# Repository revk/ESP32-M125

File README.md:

# ESP32-M125

This is hardware and software designed to be fitted within a Marsden M-125 set of medical scales.

Examples of modifications with much older prototype boards https://youtu.be/l1VAymhwtVMand  https://youtu.be/jy-5EB_Qu8Y

Takes data when SEND pressed and reports via MQTT and https. But can also work with an NFC board https://github.com/revk/ESP32-PN532 so tapping a card or tag will report ID and weight, pressing SEND for you.

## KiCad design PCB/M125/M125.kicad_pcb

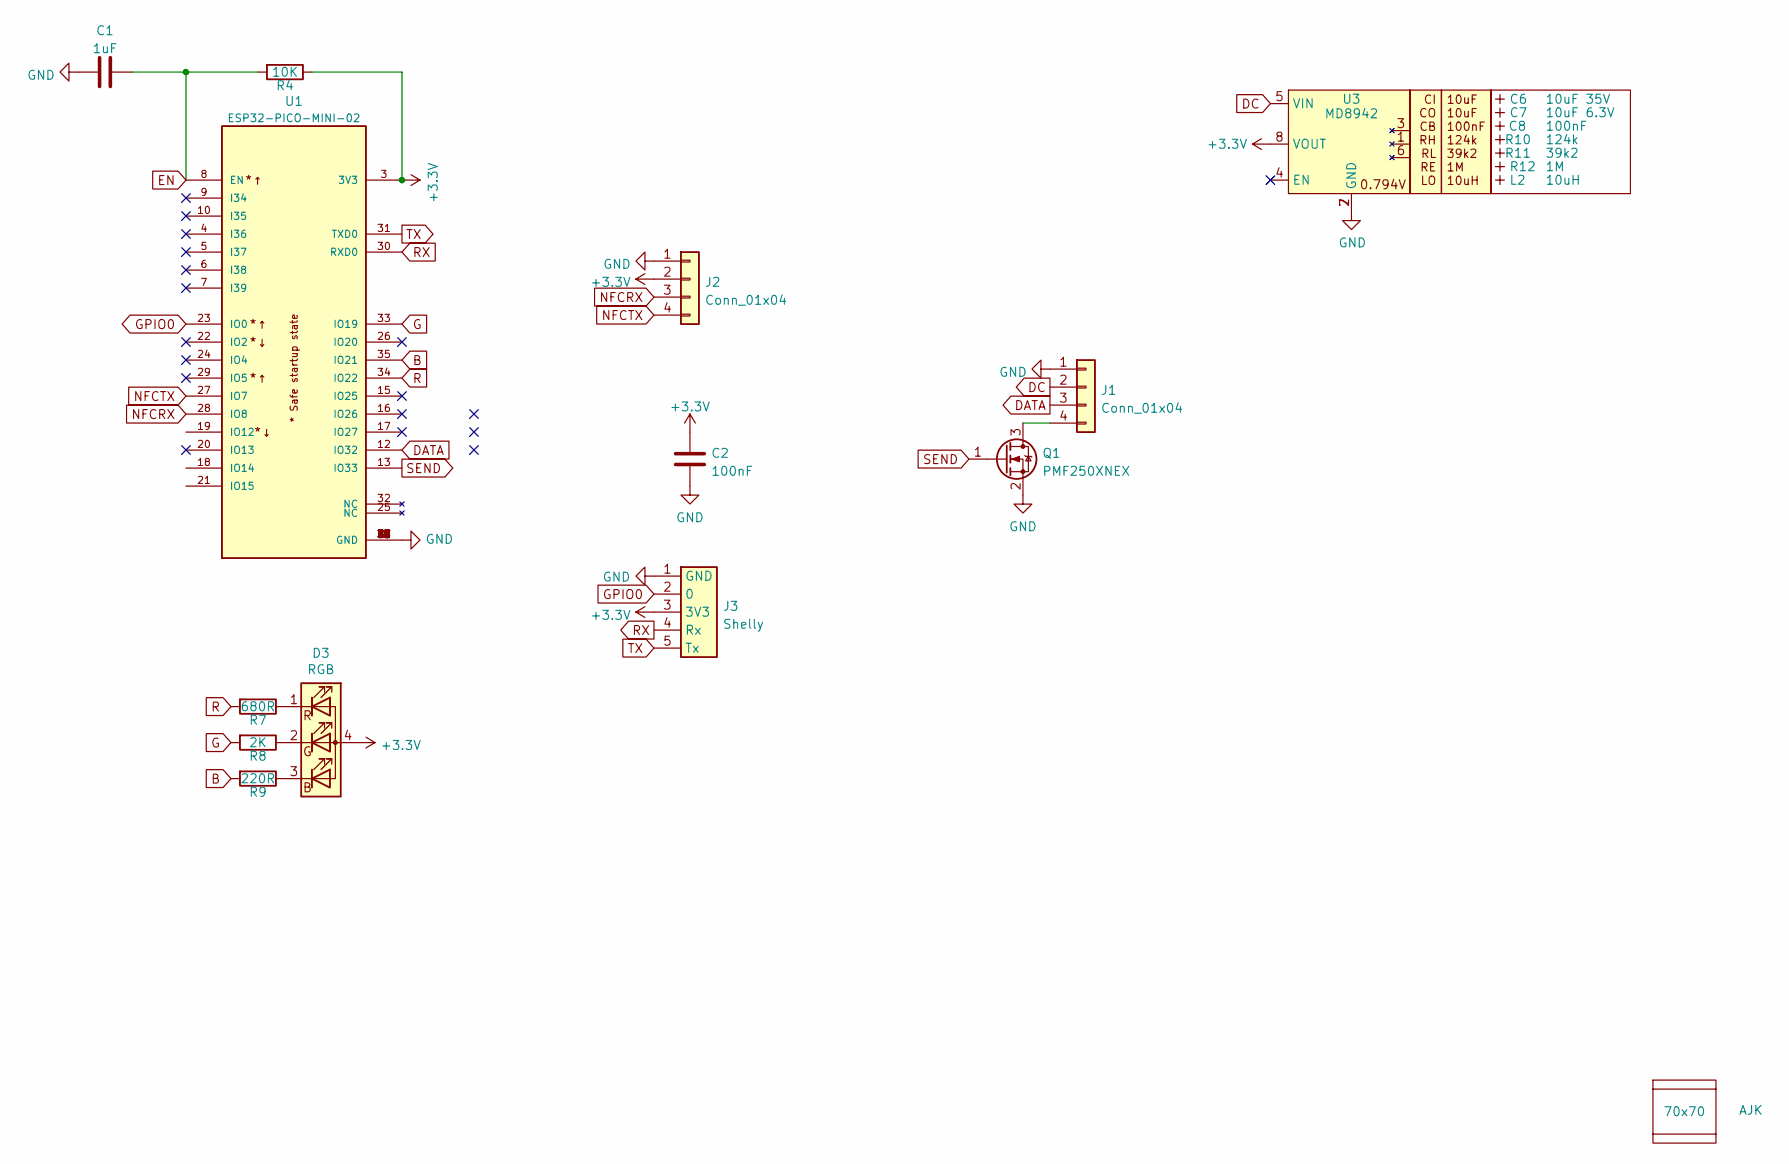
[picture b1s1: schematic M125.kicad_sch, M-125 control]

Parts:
C1: 1uF; C_0402
C2: 100nF; C_0402
C6: 10uF 35V; C_0603_; MPN C194427
C7: 10uF 6.3V; C_0603_; MPN C1691
C8: 100nF; C_0603_
D3: RGB; LED-RGB-1.6x1.6; Part No APTF1616LSEEZGKQBKC
J1, J2: Conn_01x04; PTSM-HH-4-RA
J3: Shelly
L2: 10uH; L_4x4_
Logo1: AJK
PCB1: 70x70; PCB7070
Q1: PMF250XNEX; SOT-323_SC-70; Part No PMF250XNEX
R4: 10K; R_0402
R7: 680R; R_0402
R8: 2K; R_0402
R9: 220R; R_0402
R10: 124k; R_0402_
R11: 39k2; R_0402_
R12: 1M; R_0402_
U1: ESP32-PICO-MINI-02; PARTREV v1.0
U3: MD8942; SOT-23-6-MD8942; MPN C2684786
V1, V2: VCUT70

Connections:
+3V3: C2.1, D3.4 (A), J2.2, J3.3 (3V3), R4.1, U1.3 (3V3), U3.8 (VOUT)
B: R9.2, U1.35 (IO21)
DATA: J1.3, U1.12 (IO32)
DC: J1.2, U3.5 (VIN)
EN: C1.2, R4.2, U1.8 (EN)
G: R8.2, U1.33 (IO19)
GND: C1.1, C2.2, J1.1, J2.1, J3.1 (GND), Q1.2 (S), U1.1 (GND), U1.2 (GND), U1.11 (GND), U1.14 (GND), U1.36 (GND), U1.37 (GND), U1.38 (GND), U1.39 (GND), U1.40 (GND), U1.41 (GND), U1.42 (GND), U1.43 (GND), U1.44 (GND), U1.45 (GND), U1.46 (GND), U1.47 (GND), U1.48 (GND), U1.49 (GND), U1.50 (GND), U1.51 (GND), U1.52 (GND), U1.53 (GND), U3.2 (GND), U3.7 (GND)
GPIO0: J3.2 (0), U1.23 (IO0)
NFCRX: J2.3, U1.28 (IO8)
NFCTX: J2.4, U1.27 (IO7)
unnamed: D3.3 (BK), R9.1
unnamed: D3.2 (GK), R8.1
unnamed: D3.1 (RK), R7.1
unnamed: J1.4, Q1.3 (D)
R: R7.2, U1.34 (IO22)
RX: J3.4 (Rx), U1.30 (RXD0)
SEND: Q1.1 (G), U1.13 (IO33)
TX: J3.5 (Tx), U1.31 (TXD0)

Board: 2 copper layers, 24 parts (18 on the bottom side), 18 nets, no tracks yet.

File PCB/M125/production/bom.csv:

Designator,Footprint,Quantity,Value,LCSC Part #
C1,C_0402,1,1uF,
C2,C_0402,1,100nF,
C6,C_0603_,1,10uF 50V,C1591
C7,C_0603_,1,10uF 6.3V,C1691
C8,C_0603_,1,100nF,
D3,LED-RGB-1.6x1.6,1,RGB,C264508
"J1, J2",PTSM-HH-4-RA,2,Conn_01x04,
J3,Shelly,1,Shelly,
L2,L_4x4_,1,10uH,
Q1,SOT-323_SC-70,1,PMF250XNEX,
R10,R_0402_,1,124k,
R11,R_0402_,1,39k2,
R12,R_0402_,1,1M,
R4,R_0402,1,10K,
R7,R_0402,1,680R,
R8,R_0402,1,2K,
R9,R_0402,1,220R,
U1,ESP32-PICO-MINI-02,1,ESP32-PICO-MINI-02,
U3,SOT-23-6-MD8942,1,MD8942,C2684786

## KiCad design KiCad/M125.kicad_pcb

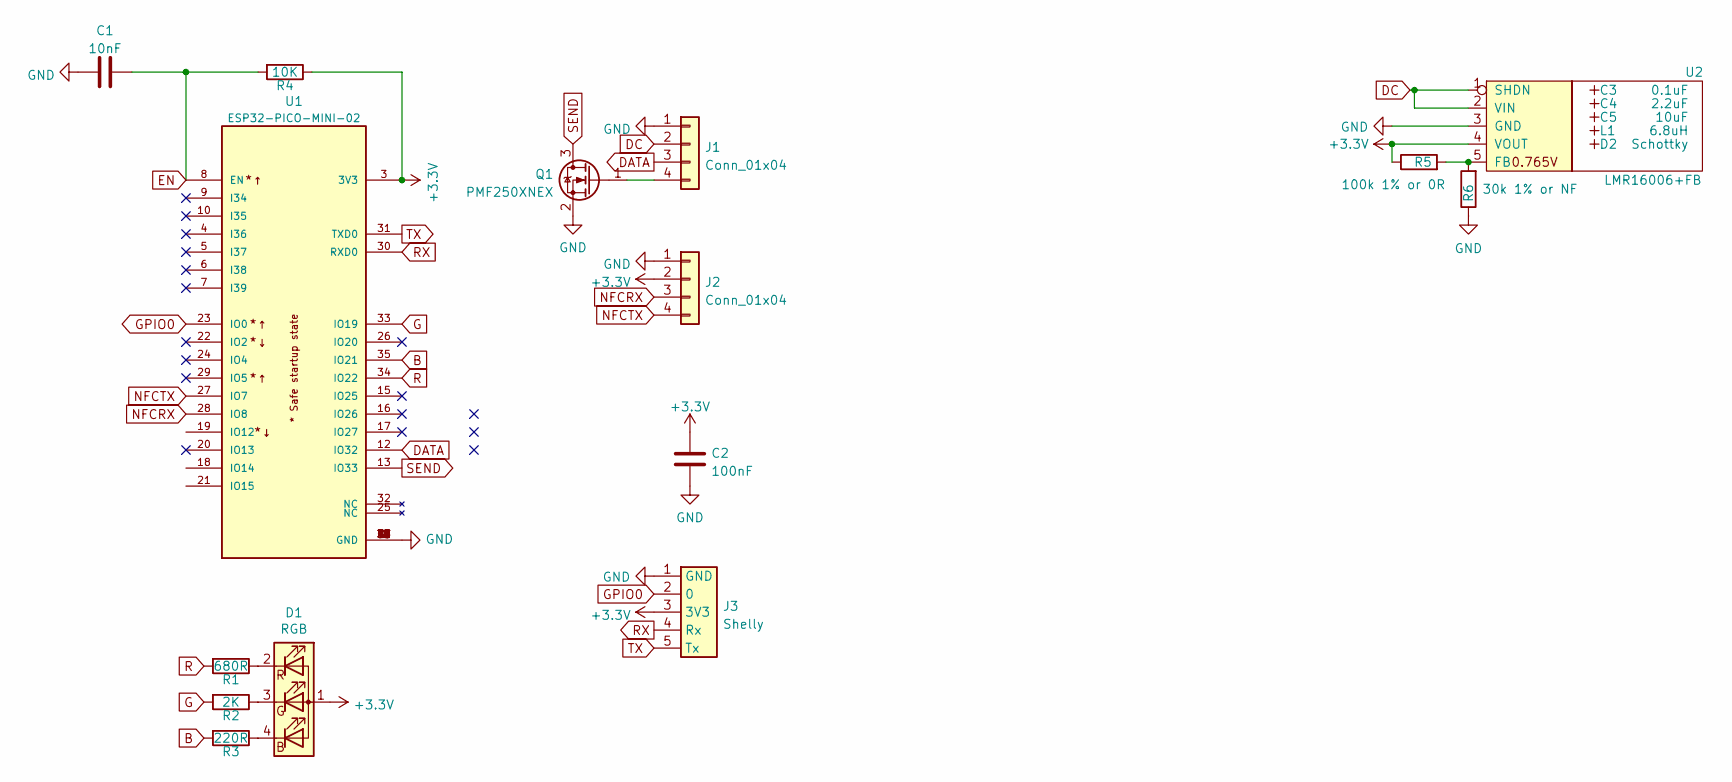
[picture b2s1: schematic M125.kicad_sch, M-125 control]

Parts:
C1: 10nF; C_0603
C2: 100nF; C_0603
C3: 0.1uF; Hidden
C4: 2.2uF; Hidden
C5: 10uF; Hidden
D1: RGB; LED-RGB-1.6x1.6; Part No APTF1616LSEEZGKQBKC
D2: Schottky; Hidden; Part No CD1206-B2100
J1, J2: Conn_01x04; Molex_MiniSPOX_H4RA
J3: Shelly
L1: 6.8uH; Hidden; Part No TYA4020
Q1: PMF250XNEX; SOT-323_SC-70; Part No PMF250XNEX
R1: 680R; R_0603
R2: 2K; R_0603
R3: 220R; R_0603
R4: 10K; R_0603
R5: 100k 1% or 0R; R_0603
R6: 30k 1% or NF; R_0603
U1: ESP32-PICO-MINI-02; PARTREV v1.0
U2: LMR16006+FB; RegulatorBlockFB; Part No LMR16006YQ3

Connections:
+3V3: C2.1, D1.1 (A), J2.2, J3.3 (3V3), R4.1, R5.1, U1.3 (3V3), U2.4 (VOUT)
B: R3.2, U1.35 (IO21)
DATA: J1.3, U1.12 (IO32)
DC: J1.2, U2.1 (SHDN), U2.2 (VIN)
EN: C1.2, R4.2, U1.8 (EN)
G: R2.2, U1.33 (IO19)
GND: C1.1, C2.2, J1.1, J2.1, J3.1 (GND), Q1.2 (S), R6.1, U1.1 (GND), U1.2 (GND), U1.11 (GND), U1.14 (GND), U1.36 (GND), U1.37 (GND), U1.38 (GND), U1.39 (GND), U1.40 (GND), U1.41 (GND), U1.42 (GND), U1.43 (GND), U1.44 (GND), U1.45 (GND), U1.46 (GND), U1.47 (GND), U1.48 (GND), U1.49 (GND), U1.50 (GND), U1.51 (GND), U1.52 (GND), U1.53 (GND), U2.3 (GND)
GPIO0: J3.2 (0), U1.23 (IO0)
NFCRX: J2.3, U1.28 (IO8)
NFCTX: J2.4, U1.27 (IO7)
unnamed: D1.2 (RK), R1.1
unnamed: D1.3 (GK), R2.1
unnamed: D1.4 (BK), R3.1
unnamed: J1.4, Q1.1 (G)
unnamed: R5.2, R6.2, U2.5 (FB)
R: R1.2, U1.34 (IO22)
RX: J3.4 (Rx), U1.30 (RXD0)
SEND: Q1.3 (D), U1.13 (IO33)
TX: J3.5 (Tx), U1.31 (TXD0)

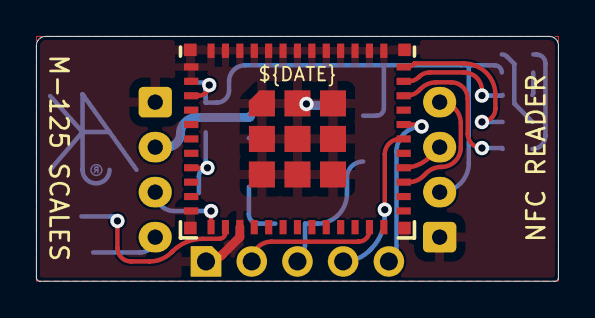
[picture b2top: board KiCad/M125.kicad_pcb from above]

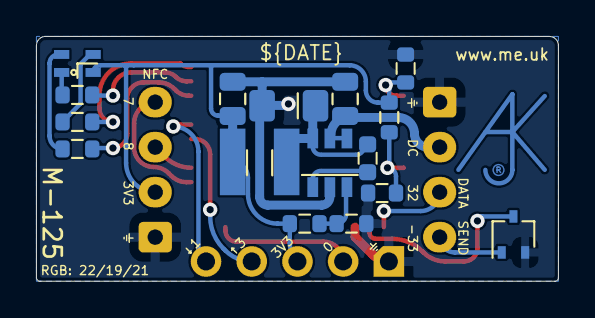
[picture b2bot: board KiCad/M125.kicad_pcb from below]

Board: 2 copper layers, 29.0 x 13.6 mm, 21 parts (18 on the bottom side), 19 nets.

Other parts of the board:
Logo1: AJK

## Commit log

2022-06-25 Starting code
2022-06-25 More startup
2022-06-25 Tweak PCBs
2022-06-27 New PCB
2022-06-27 Case
2022-06-27 Get started
2022-06-27 mask
2022-06-27 Started on serial and NFC code
2022-06-27 Basic operation
2022-06-27 Auto upgrade
2022-06-28 Tidy PCB for placement of regulator parts
2022-12-31 Library update
2023-04-17 Release
2023-06-15 Tidy
2023-07-04 checkpoint
2024-03-03 Beta
2025-01-23 PCB Update
